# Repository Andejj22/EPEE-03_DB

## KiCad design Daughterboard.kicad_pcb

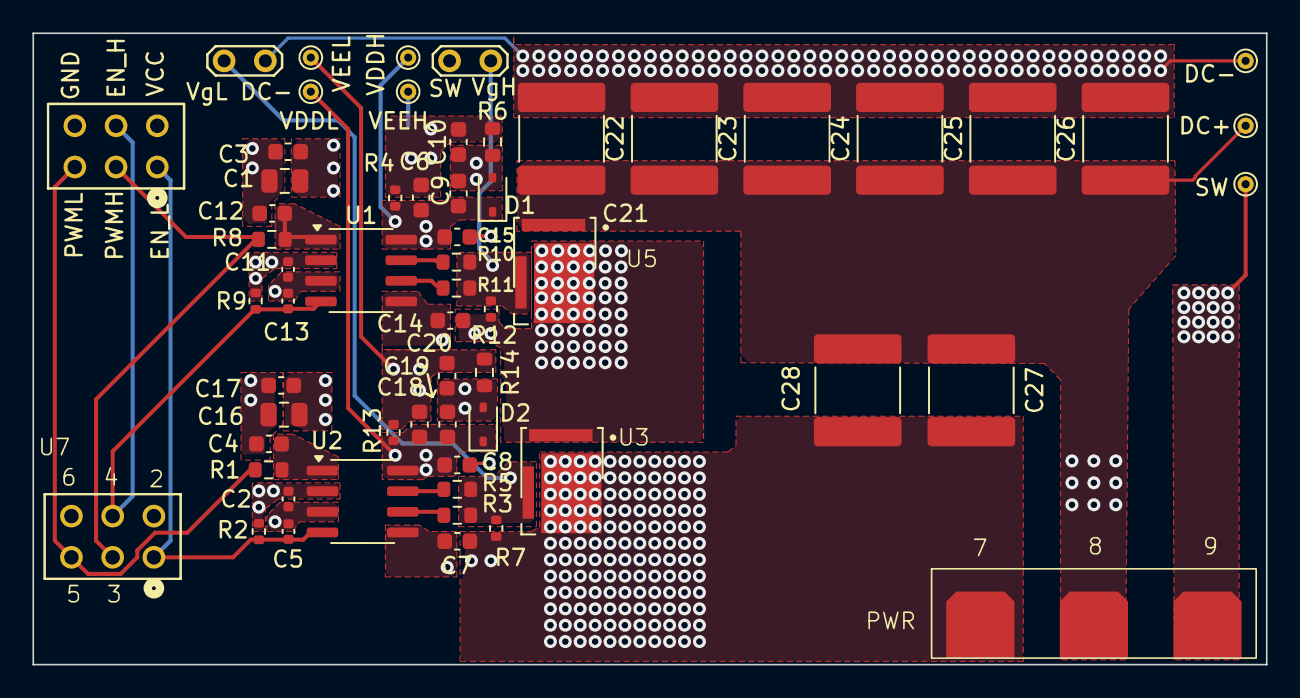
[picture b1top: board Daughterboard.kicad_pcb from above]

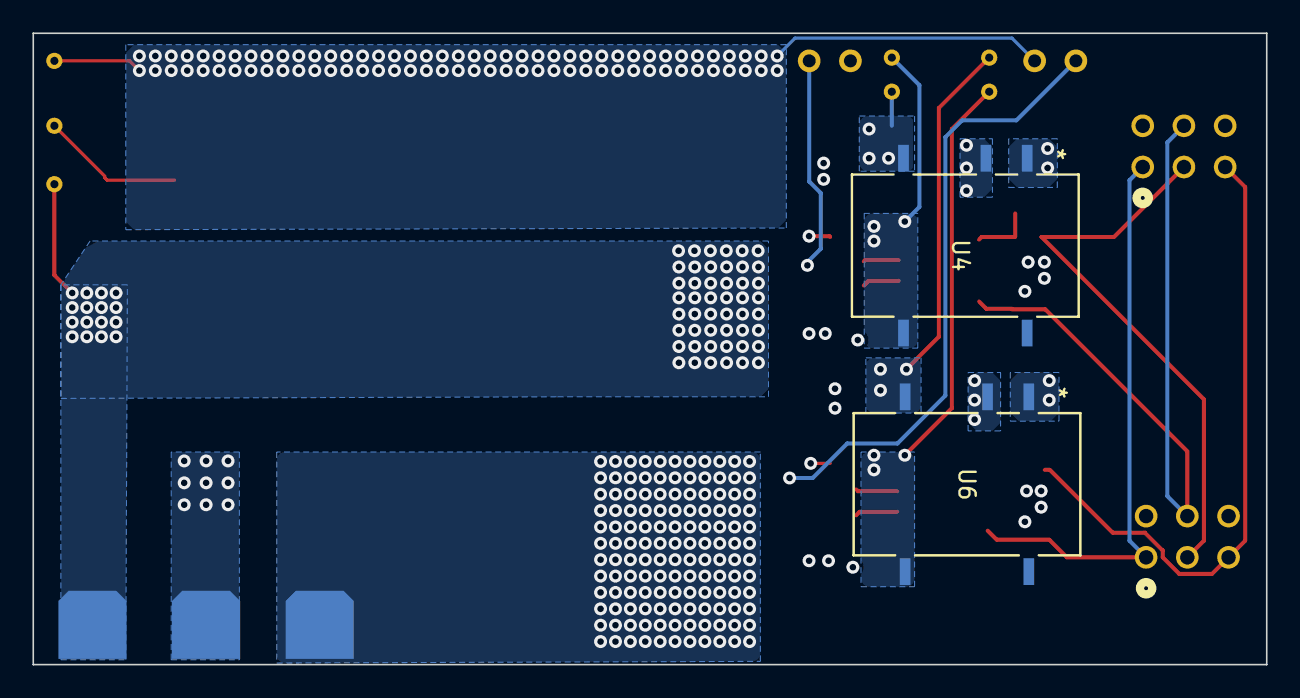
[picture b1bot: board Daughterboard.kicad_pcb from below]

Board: 4 copper layers, 76.0 x 38.9 mm, 61 parts (2 on the bottom side), 21 nets.

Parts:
C1, C16: 10u; C_0805_2012Metric
C2, C5, C11, C13: 0.1u 50 V; C_0402_1005Metric
C3, C6, C17, C18: 4.7u 16 V; C_0603_1608Metric
C4, C12: 22p; C_0603_1608Metric
C7, C8, C9, C10, C14, C15, C19, C20: 1u 50 V; C_0603_1608Metric
C21, C22, C23, C24, C25, C26, C27, C28: 0.1u 650 V; C_2220_5750Metric
D1, D2: 5.8; D_SOD-323
DC+: TestPoint; TestPoint_THTPad_D1.0mm_Drill0.5mm
DC-: TestPoint; TestPoint_THTPad_D1.0mm_Drill0.5mm
GND: Conn_02x03_Odd_Even; CON6_2X3_TU_TSW_SAI
R1, R8: 0; R_0603_1608Metric
R2, R9: 3.3k; R_0402_1005Metric
R3, R11: 2; R_0603_1608Metric
R4, R13: 2.2k; R_0402_1005Metric
R5, R10: 10; R_0603_1608Metric
R6, R14: 1k; R_0603_1608Metric
R7, R12: 10k; R_0402_1005Metric
SW: TestPoint; TestPoint_THTPad_D1.0mm_Drill0.5mm
SW#2: TestPoint_2Pole; TestPoint_2Pads_Pitch2.54mm_Drill0.8mm
U1, U2: SI8271GB-IS; SOIC-8_3.9x4.9mm_P1.27mm
U3, U5: GS61004B; GS6XXX4B
U4, U6: IES0105S09
U7: DB_to_MB_conn
VDDH: TestPoint; TestPoint_THTPad_D1.0mm_Drill0.5mm
VDDL: TestPoint; TestPoint_THTPad_D1.0mm_Drill0.5mm
VEEH: TestPoint; TestPoint_THTPad_D1.0mm_Drill0.5mm
VEEL: TestPoint; TestPoint_THTPad_D1.0mm_Drill0.5mm
VgL DC-: TestPoint_2Pole; TestPoint_2Pads_Pitch2.54mm_Drill0.8mm

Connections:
/VgH: R10.2, R11.2, R12.1, SW#2.2, U5.2 (G)
/VgL: R3.2, R5.2, R7.1, U3.2 (G), VgL DC-.2
DC+: C21.1, C22.1, C23.1, C24.1, C25.1, C26.1, C27.1, C28.1, DC+.1, U5.1 (D), U7.8 (DC+)
DC-: C7.2, C8.2, C19.2, C20.1, C21.2, C22.2, C23.2, C24.2, C25.2, C26.2, C27.2, C28.2, D2.2 (A), DC-.1, R7.2, R14.1, U3.3 (S), U7.7 (DC-), VgL DC-.1
ENABLEH: C13.1, GND.4, R9.2, U1.4 (EN), U7.4 (ENABLEH)
ENABLEL: C5.1, GND.1, R2.2, U2.4 (EN), U7.1 (ENABLEL)
GND: C1.2, C2.2, C3.2, C4.2, C5.2, C11.2, C12.2, C13.2, C16.2, C17.2, GND.6, U1.3 (GNDI), U2.3 (GNDI), U4.1 (-Vin), U6.1 (-Vin), U7.6 (GND)
unnamed: C12.1, R8.2, U1.1 (VI)
unnamed: R10.1, U1.7 (VO+)
unnamed: R11.1, U1.6 (VO-)
unnamed: C4.1, R1.2, U2.1 (VI)
unnamed: R5.1, U2.7 (VO+)
unnamed: R3.1, U2.6 (VO-)
PWMH: GND.3, R8.1, U7.3 (PWMH)
PWML: GND.5, R1.1, U7.5 (PWML)
SW: C9.2, C10.1, C14.2, C15.2, D1.2 (A), R6.1, R12.2, SW.1, SW#2.1, U3.1 (D), U5.3 (S), U7.9 (SW)
VCC+5V: C1.1, C2.1, C3.1, C11.1, C16.1, C17.1, GND.2, R2.1, R9.1, U1.2 (VDDI), U2.2 (VDDI), U4.2 (+Vin), U6.2 (+Vin), U7.2 (VCC+5V)
VDDH: C6.1, C9.1, C15.1, D1.1 (K), R4.1, U1.8 (VDD), U4.5 (+Vout), VDDH.1
VDDL: C8.1, C18.1, C19.1, D2.1 (K), R13.1, U2.8 (VDD), U6.5 (+Vout), VDDL.1
VEEH: C6.2, C10.2, C14.1, R4.2, R6.2, U1.5 (GND), U4.4 (-Vout), VEEH.1
VEEL: C7.1, C18.2, C20.2, R13.2, R14.2, U2.5 (GND), U6.4 (-Vout), VEEL.1

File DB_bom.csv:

Comment,Designator,Footprint,LCSC Part #
"10u Unpolarized capacitor,""C1,C16"",C_0805_2012Metric,C15850"
"0.1u 50 V Unpolarized capacitor,""C2,C5,C11,C13"",C_0402_1005Metric,C307331"
"4.7u 16 V Unpolarized capacitor,""C3,C6,C17,C18"",C_0603_1608Metric,C19666"
"1u 50 V Unpolarized capacitor,""C7,C8,C9,C10,C14,C15,C19,C20"",C_0603_1608Metric,C15849 "
"5.8 Zener diode,""D1,D2"",D_SOD-323,C2891792"
"3.3k Resistor,""R2,R9"",R_0402_1005Metric,C25890"
"2 Resistor,""R3,R11"",R_0603_1608Metric,C22977"
"2.2k Resistor,""R4,R13"",R_0402_1005Metric,C25879"
"10 Resistor,""R5,R10"",R_0603_1608Metric,C22859"
"1k Resistor,""R6,R14"",R_0603_1608Metric,C21190"
"10k Resistor,""R7,R12"",R_0402_1005Metric,C25744"

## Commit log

2024-04-02 init
2024-04-02 start layout design, component placement
2024-04-03 initial version for commenting
2024-04-11 fixed after comments
2024-04-14 second version after comments
2024-04-17 gerbers, drill files and pick-and-place added, deleted unneccessary items from BOM
2024-04-17 deleted old bom
2024-04-17 deleted extra pick-and-place files
